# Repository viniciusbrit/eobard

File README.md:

# Meet Eobard, a split 34 key ortholinear keyboard.
Current Hardware Revision: 0.2.8

## Project Description
Eobard is an ortholinear 34 key split keyboard made for my personal needs. Inspired by the [Ferris](https://github.com/pierrechevalier83/ferris).

The columns are spaced out vertically so as to provide the most comfortable typing experience for my hand size. It is designed to be cheap to manufacture and simple to assemble. The single PCB is dual sided, only having to be flipped around for assembly of the other side.

<details>
<summary>Hardware Tasks</summary>

- [x] Design Layout. 
- [x] Design PCB & Plate.
- [x] Generate Gerbers.
- [x] Build Prototype.
- [ ] Write Build Guide with images.
- [x] Change 5th Column Spacing to a more comfortable distance.
- [ ] Make the right side's BOOTSEL button more accessible after soldering.
- [x] Get permission to use the BTW creature in silkscreen.
- [x] Change Placement of TRRS footprints on PCB.
- [x] Move Thumb Keys to Rows 4 and 5.
- [x] Make board diodeless.
- [ ] Release First Version.
</details>

<details>
<summary>Software Tasks</summary>

- [x] Write US English Base Layout.
- [x] Write EU Portuguese Base Layout.
</details>

## Images

## Bill of materials
* Raspberry Pi Pico [x2]
* [PJ-320A 3.5mm Audio Jack [x2]](https://www.lcsc.com/product-detail/Audio-Connectors_Hong-Cheng-HC-PJ-320A_C7501806.html)
* Cherry MX Style Switches [x34]
* 4mm M2 Standoff [x9]
* 3mm M2 Screws [x18]
* 01x20 2.54mm Standard Male Pin Headers [x4] [If Pico doesn't have them pre-soldered]

## Ordering PCBs
Dragging and dropping the provided Gerber zips onto JLCPCB or other manufacturer's websites should work just fine. Make sure the plate PCB is 1mm thick and the main pcb is 1.6mm thick.

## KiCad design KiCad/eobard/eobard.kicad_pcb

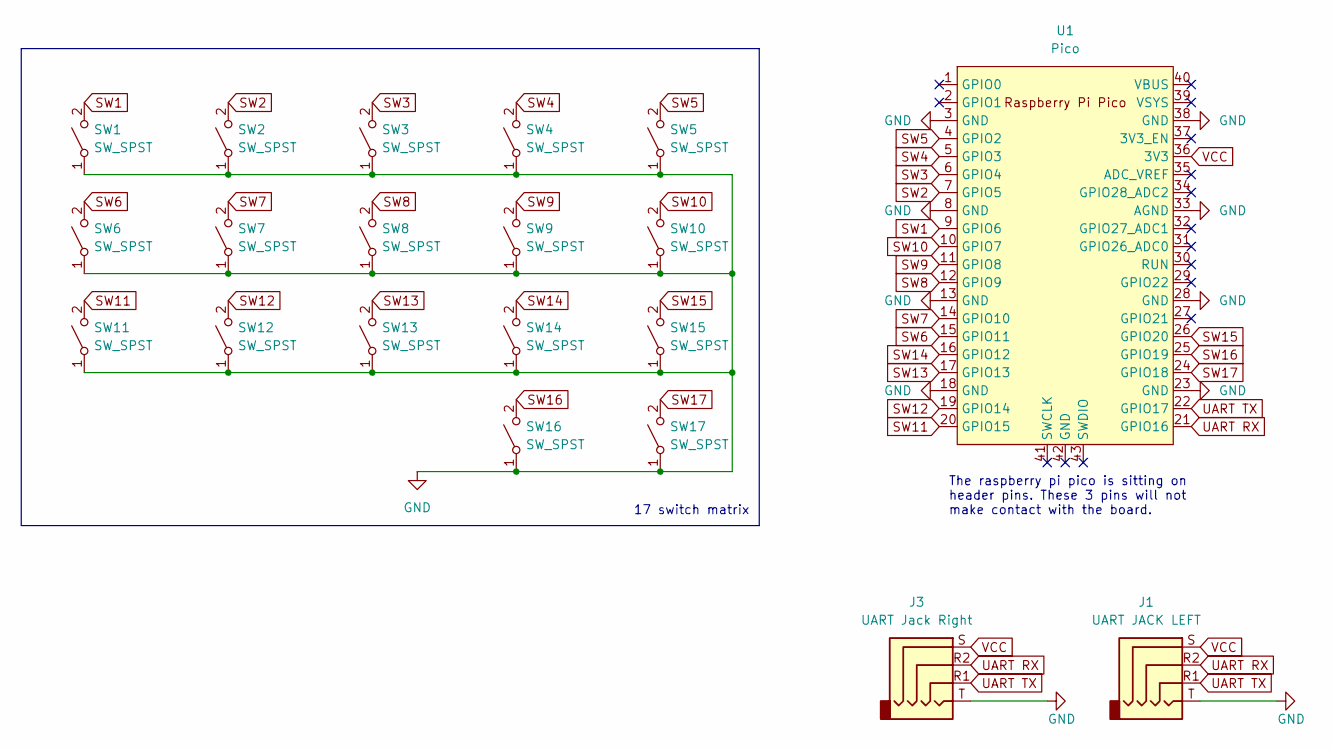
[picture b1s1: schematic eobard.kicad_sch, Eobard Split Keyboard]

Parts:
J1: UART JACK LEFT; PJ-320A
J3: UART Jack Right; PJ-320A
SW1, SW2, SW3, SW4, SW5, SW6, SW7, SW8, SW9, SW10, SW11, SW12, SW13, SW14, SW15, SW16, SW17: SW_SPST; SW_MX_reversible
U1: Pico; RPi_Pico_SMD_TH

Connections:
GND: J1.T, J3.T, SW1.1 (A), SW2.1 (A), SW3.1 (A), SW4.1 (A), SW5.1 (A), SW6.1 (A), SW7.1 (A), SW8.1 (A), SW9.1 (A), SW10.1 (A), SW11.1 (A), SW12.1 (A), SW13.1 (A), SW14.1 (A), SW15.1 (A), SW16.1 (A), SW17.1 (A), U1.3 (GND), U1.8 (GND), U1.13 (GND), U1.18 (GND), U1.23 (GND), U1.28 (GND), U1.33 (AGND), U1.38 (GND)
SW1: SW1.2 (B), U1.9 (GPIO6)
SW2: SW2.2 (B), U1.7 (GPIO5)
SW3: SW3.2 (B), U1.6 (GPIO4)
SW4: SW4.2 (B), U1.5 (GPIO3)
SW5: SW5.2 (B), U1.4 (GPIO2)
SW6: SW6.2 (B), U1.15 (GPIO11)
SW7: SW7.2 (B), U1.14 (GPIO10)
SW8: SW8.2 (B), U1.12 (GPIO9)
SW9: SW9.2 (B), U1.11 (GPIO8)
SW10: SW10.2 (B), U1.10 (GPIO7)
SW11: SW11.2 (B), U1.20 (GPIO15)
SW12: SW12.2 (B), U1.19 (GPIO14)
SW13: SW13.2 (B), U1.17 (GPIO13)
SW14: SW14.2 (B), U1.16 (GPIO12)
SW15: SW15.2 (B), U1.26 (GPIO20)
SW16: SW16.2 (B), U1.25 (GPIO19)
SW17: SW17.2 (B), U1.24 (GPIO18)
UART RX: J1.R2, J3.R2, U1.21 (GPIO16)
UART TX: J1.R1, J3.R1, U1.22 (GPIO17)
VCC: J1.S, J3.S, U1.36 (3V3)

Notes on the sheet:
The raspberry pi pico is sitting on header pins. These 3 pins will not make contact with the board.
17 switch matrix

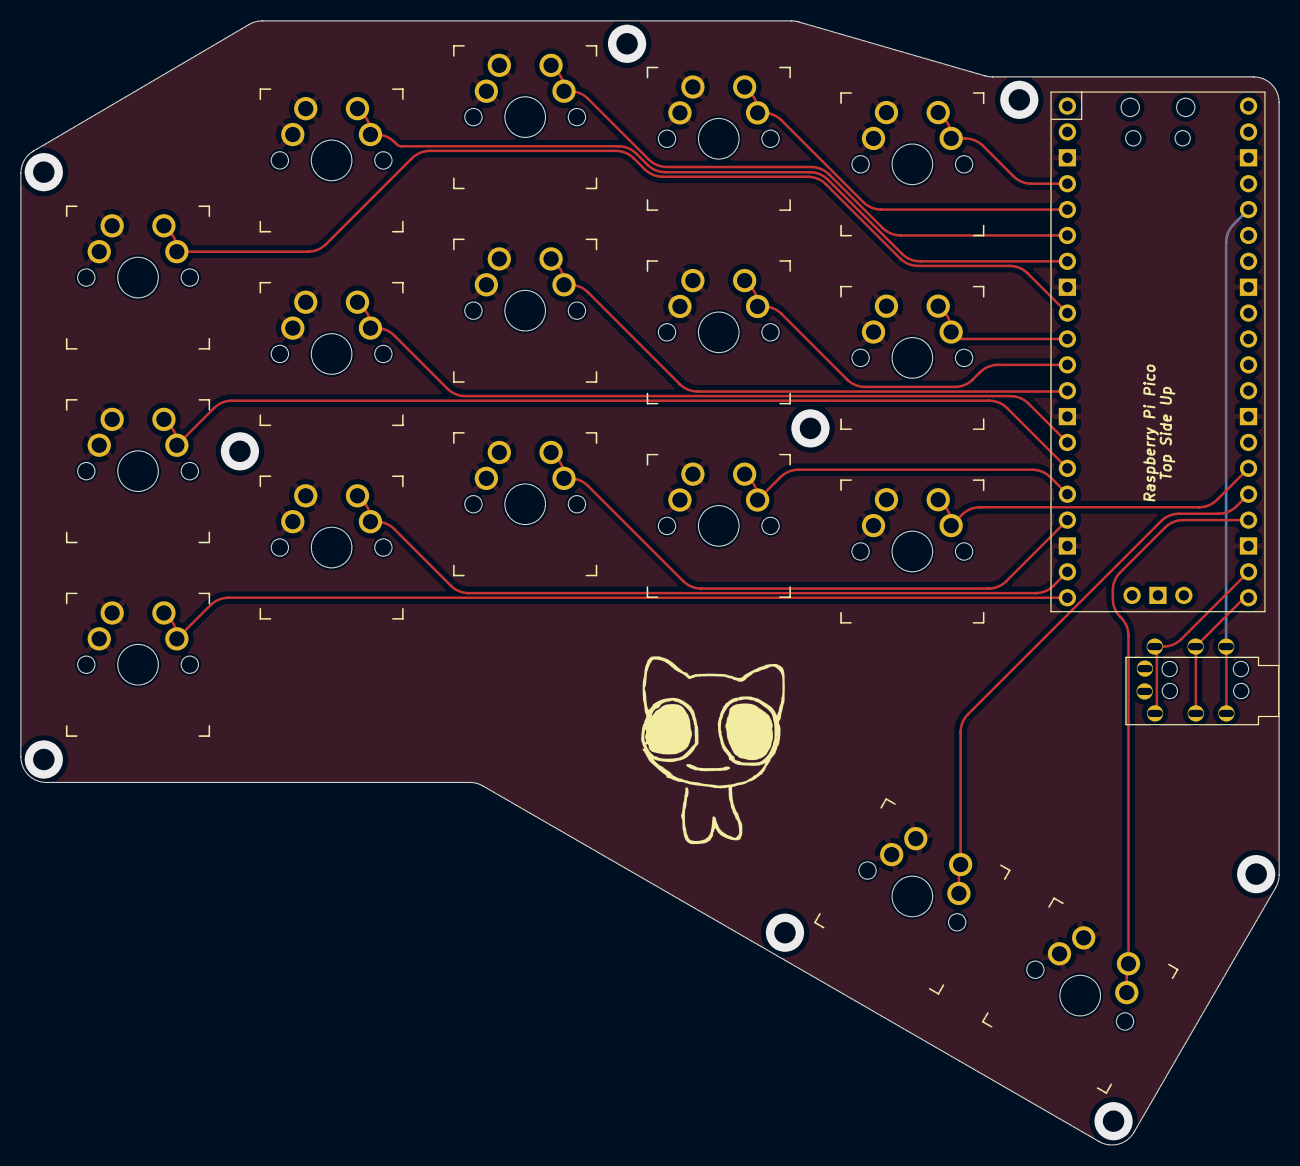
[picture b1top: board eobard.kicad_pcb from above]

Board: 2 copper layers, 123.5 x 110.3 mm, 20 parts (1 on the bottom side), 21 nets.

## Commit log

2024-01-08 Added README & KiCad Files
2024-01-08 Updated KiCad Files
2024-01-08 Updated Plate Mounting Holes
2024-01-08 Updated Image & Image Size
2024-01-12 Fixed Silkscreen Error & Changed Mounting Hole Position
2024-01-12 Fixed Footprint Error
2024-01-12 Removed Old Plate, Slight PCB Changes
2024-01-12 Updated PCB Gerbers
2024-01-12 Updated Board Design
2024-01-12 Added New Plate Design
2024-02-04 Added Keyboard Firmware
2024-02-04 Reorganized Project Images
2024-02-08 Finished Layers
2024-02-08 Small README.md Fix
2024-02-08 Small layout adjust
2024-02-09 Update LICENSE
    Changing license over from MIT to GNU GPL 3
2024-02-09 Updated Layout
    Still trying to get OLED to work
2024-02-14 Updated Firmware
2024-02-17 Updated Layout
    Properly formatted the layout for Portuguese ISO Locales
2024-02-17 Fixed A Single Key
2024-02-17 Tiny Update
2024-02-18 Updated README.md
    Cleaned up some rough spots
2024-02-18 Reorganized Project Files
2024-02-18 Updated Layouts
    Added Print Screen
2024-02-18 Updated Hardware Goals
2024-02-18 Fixed Small Formatting Issue
2024-02-18 Tiny Fix
2024-02-18 Fixed Typos
2024-02-19 Small Layout Change
2024-02-20 Updated Tasks
2024-03-25 Updated Project
    Started work on version 1.0.
    Dealing with a few bugs on KiCad right now...
    Reorganized file structure
2024-03-26 Finished Initial Board Layout
    Improving on the prototype. Gerbers are inside kicad folder.
2024-03-26 Tiny Layout Change
2024-03-26 Updated Project Progress
2024-03-26 Updated BOM
    Bill of materials has been updated to reflect new design requirements.
2024-04-08 Update README.md
    Fixed a typo, added new hardware task that was completed.
